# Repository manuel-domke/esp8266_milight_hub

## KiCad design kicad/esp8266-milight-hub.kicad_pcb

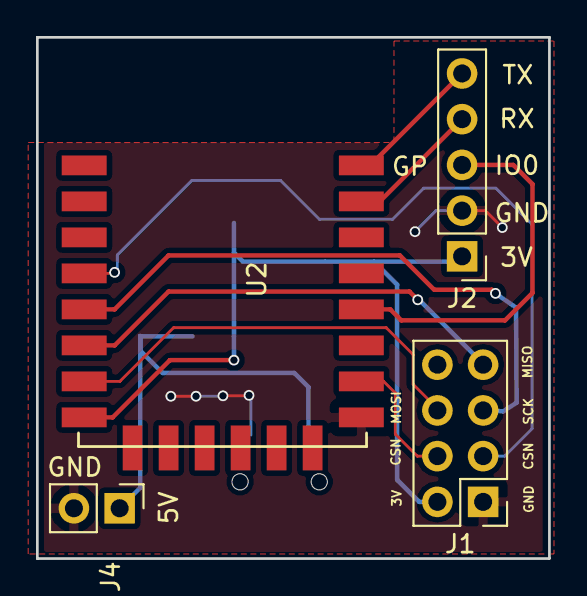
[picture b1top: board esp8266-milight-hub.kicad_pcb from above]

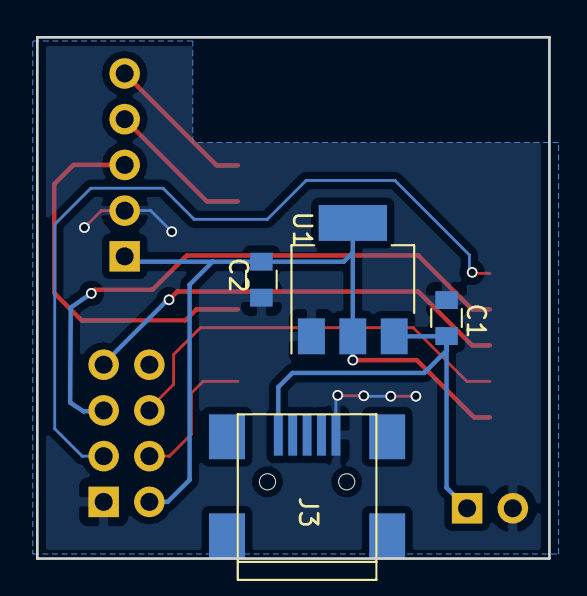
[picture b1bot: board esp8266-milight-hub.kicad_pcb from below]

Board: 2 copper layers, 28.4 x 29.0 mm, 8 parts (4 on the bottom side), 11 nets.

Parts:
C1, C2: 10uF; C_0805
J1: Conn_02x04_Odd_Even; Pin_Header_Straight_2x04_Pitch2.54mm
J2: Conn_01x05_Female; Pin_Header_Straight_1x05_Pitch2.54mm
J3: USB_OTG; USB_Mini-B
J4: Conn_01x02_Female; Pin_Header_Straight_1x02_Pitch2.54mm
U1: LM1117-3.3; SOT-223-3Lead_TabPin2
U2: ESP-12E; ESP-12E_SMD

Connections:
+3V3: C2.1, J1.2, J2.1, U1.2, U2.8
+5V: C1.1, J3.1, J4.1, U1.3
CE: J1.3, U2.4
CSN: J1.4, U2.10
GND: C1.2, C2.2, J1.1, J2.2, J3.5, J4.2, U1.1, U2.9
MOSI: J1.6, U2.7
unnamed: J1.7, U2.6
unnamed: J2.3, U2.12
unnamed: J2.4, U2.15
unnamed: J2.5, U2.16
SCK: J1.5, U2.5

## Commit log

2017-09-05 Added KiCaD PCB
